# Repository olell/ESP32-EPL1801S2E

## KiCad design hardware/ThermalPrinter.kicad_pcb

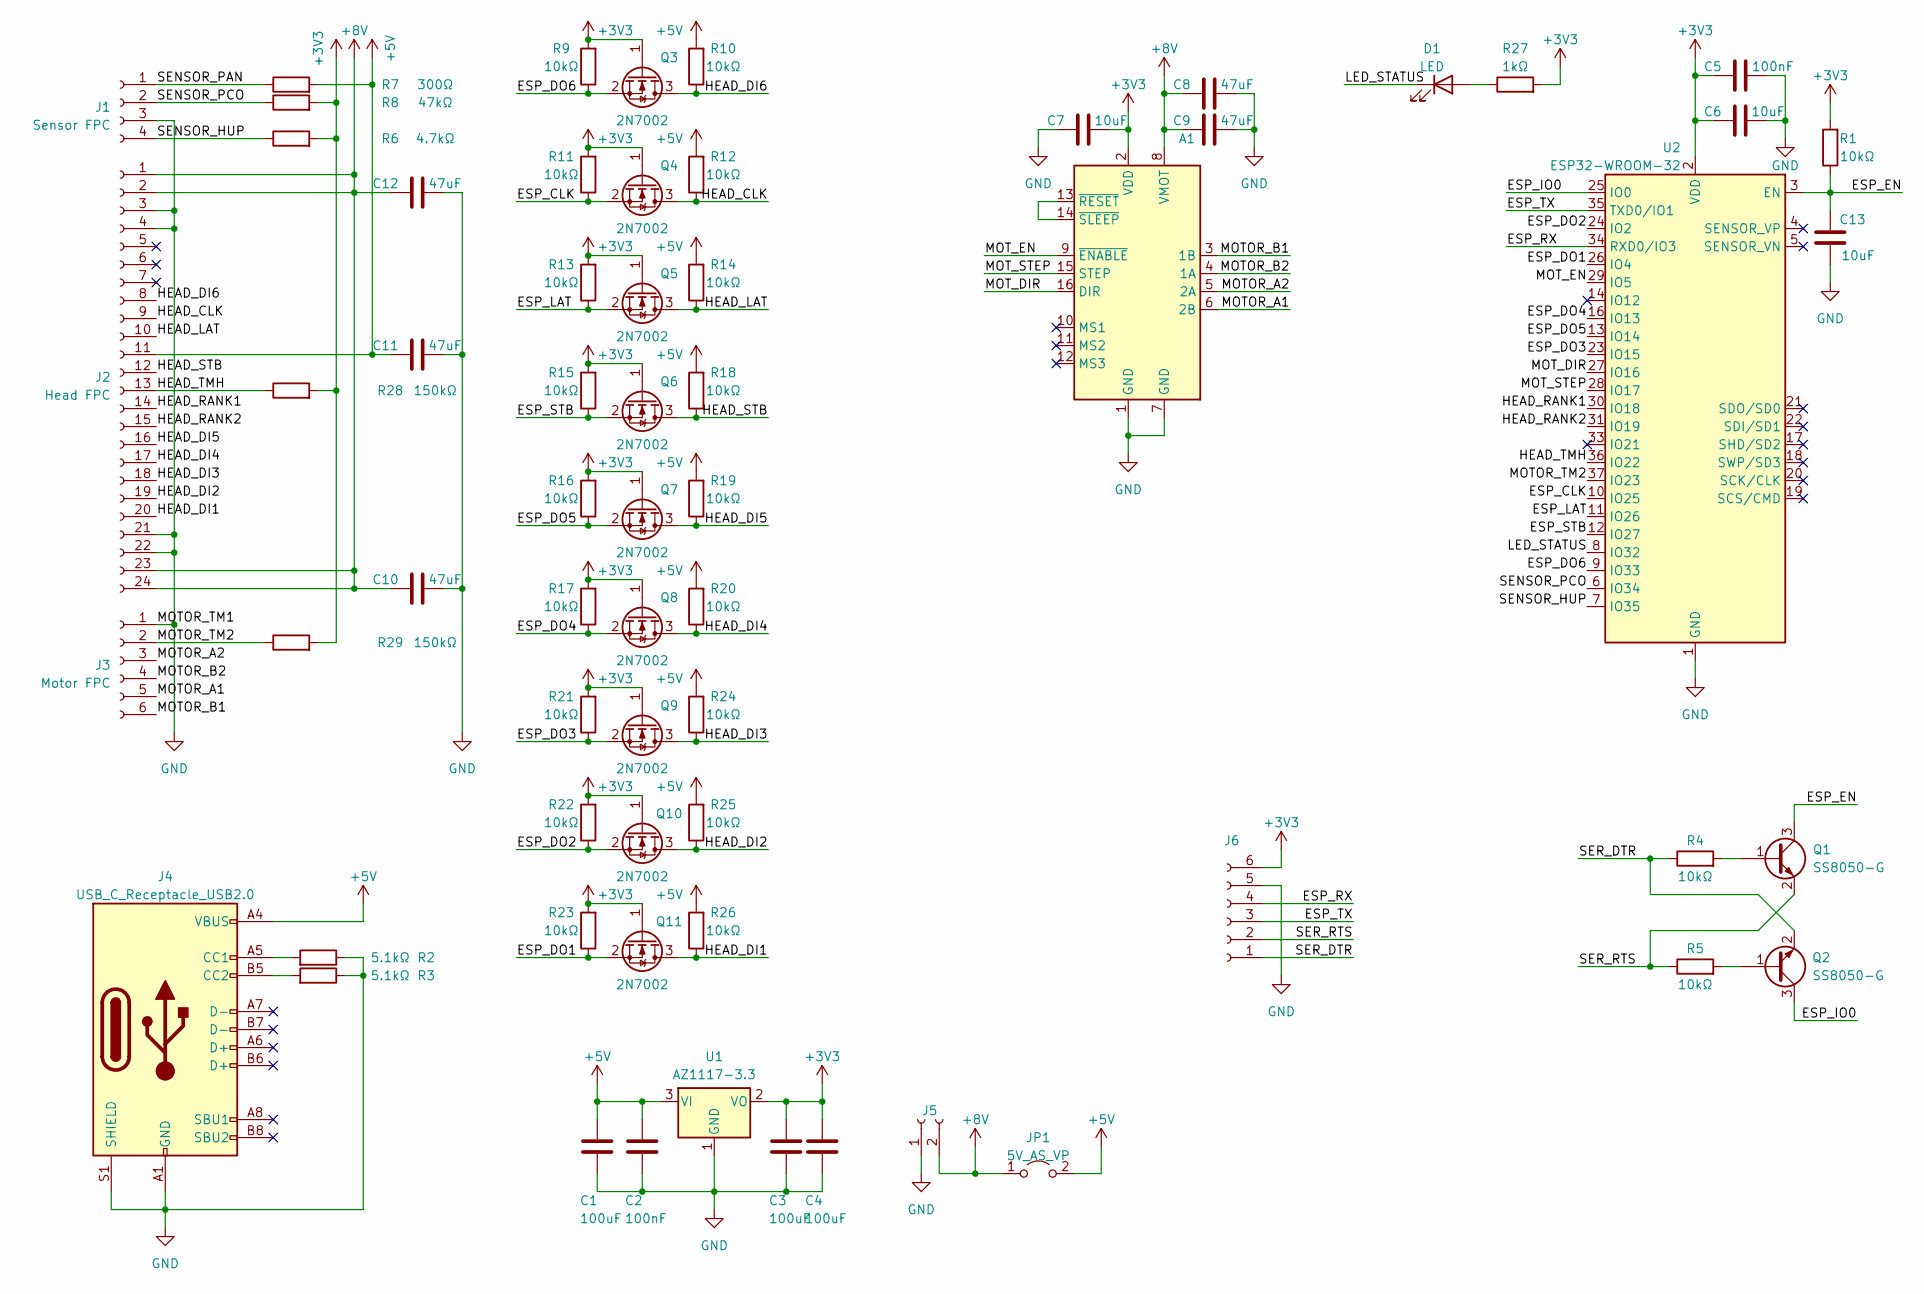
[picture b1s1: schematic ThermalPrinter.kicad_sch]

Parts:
A1: Pololu_Breakout_A4988; Pololu_Breakout-16_15.2x20.3mm
C1, C3, C4: 100uF; C_1206_3216Metric; LCSC C15008
C2, C5: 100nF; C_0603_1608Metric; LCSC C14663
C6, C7, C13: 10uF; C_0603_1608Metric; LCSC C19702
C8, C9, C10, C11, C12: 47uF; C_1206_3216Metric; LCSC C96123
D1: LED; LED_0603_1608Metric; LCSC C2286
J1: Sensor FPC; Molex_200528-0040_1x04-1MP_P1.00mm_Horizontal; LCSC C13750
J2: Head FPC; Molex_200528-0240_1x24-1MP_P1.00mm_Horizontal; LCSC C262376
J3: Motor FPC; Molex_200528-0060_1x06-1MP_P1.00mm_Horizontal; LCSC C72727
J4: USB_C_Receptacle_USB2.0; USB_C_Receptacle_HRO_TYPE-C-31-M-12; LCSC C2988369
J5: Conn_01x02_Socket; PinHeader_1x02_P2.54mm_Vertical
J6: Conn_01x06_Socket; PinSocket_1x06_P2.54mm_Vertical
JP1: 5V_AS_VP; PinSocket_1x02_P2.54mm_Vertical
Q1, Q2: SS8050-G; SOT-23; LCSC C2150
Q3, Q4, Q5, Q6, Q7, Q8, Q9, Q10, Q11: 2N7002; SOT-23; LCSC C8545
R1, R4, R5, R9, R10, R11, R12, R13, R14, R15, R16, R17, R18, R19, R20, R21, R22, R23, R24, R25, R26: 10kΩ; R_0603_1608Metric; LCSC C25804
R2, R3: 5.1kΩ; R_0603_1608Metric; LCSC C23186
R6: 4.7kΩ; R_0603_1608Metric; LCSC C23162
R7: 300Ω; R_0603_1608Metric; LCSC C23025
R8: 47kΩ; R_0603_1608Metric; LCSC C25819
R27: 1kΩ; R_0603_1608Metric; LCSC C21190
R28, R29: 150kΩ; R_0603_1608Metric; LCSC C22807
U1: AZ1117-3.3; SOT-223-3_TabPin2; LCSC C6186
U2: ESP32-WROOM-32; LCSC C529582

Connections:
+3V3: A1.2 (VDD), C3.1, C4.1, C5.1, C6.1, C7.2, J6.6, Q3.1 (G), Q4.1 (G), Q5.1 (G), Q6.1 (G), Q7.1 (G), Q8.1 (G), Q9.1 (G), Q10.1 (G), Q11.1 (G), R1.2, R6.2, R8.2, R9.2, R11.2, R13.2, R15.2, R16.2, R17.2, R21.2, R22.2, R23.2, R27.2, R28.2, R29.2, U1.2 (VO), U2.2 (VDD)
+5V: C1.1, C2.1, C11.1, J2.11, J4.A4 (VBUS), J4.A9 (VBUS), J4.B4 (VBUS), J4.B9 (VBUS), JP1.2 (B), R7.2, R10.2, R12.2, R14.2, R18.2, R19.2, R20.2, R24.2, R25.2, R26.2, U1.3 (VI)
+8V: A1.8 (VMOT), C8.1, C9.1, C10.1, C12.1, J2.1, J2.2, J2.23, J2.24, J5.2, JP1.1 (A)
/ESP_CLK: Q4.2 (S), R11.1, U2.10 (IO25)
/ESP_DO1: Q11.2 (S), R23.1, U2.26 (IO4)
/ESP_DO2: Q10.2 (S), R22.1, U2.24 (IO2)
/ESP_DO3: Q9.2 (S), R21.1, U2.23 (IO15)
/ESP_DO4: Q8.2 (S), R17.1, U2.16 (IO13)
/ESP_DO5: Q7.2 (S), R16.1, U2.13 (IO14)
/ESP_DO6: Q3.2 (S), R9.1, U2.9 (IO33)
/ESP_EN: C13.2, Q1.3 (C), R1.1, U2.3 (EN)
/ESP_IO0: Q2.3 (C), U2.25 (IO0)
/ESP_LAT: Q5.2 (S), R13.1, U2.11 (IO26)
/ESP_RX: J6.4, U2.34 (RXD0/IO3)
/ESP_STB: Q6.2 (S), R15.1, U2.12 (IO27)
/ESP_TX: J6.3, U2.35 (TXD0/IO1)
/HEAD_CLK: J2.9, Q4.3 (D), R12.1
/HEAD_DI1: J2.20, Q11.3 (D), R26.1
/HEAD_DI2: J2.19, Q10.3 (D), R25.1
/HEAD_DI3: J2.18, Q9.3 (D), R24.1
/HEAD_DI4: J2.17, Q8.3 (D), R20.1
/HEAD_DI5: J2.16, Q7.3 (D), R19.1
/HEAD_DI6: J2.8, Q3.3 (D), R10.1
/HEAD_LAT: J2.10, Q5.3 (D), R14.1
/HEAD_RANK1: J2.14, U2.30 (IO18)
/HEAD_RANK2: J2.15, U2.31 (IO19)
/HEAD_STB: J2.12, Q6.3 (D), R18.1
/HEAD_TMH: J2.13, R28.1, U2.36 (IO22)
/LED_STATUS: D1.1 (K), U2.8 (IO32)
/MOTOR_A1: A1.6 (2B), J3.5
/MOTOR_A2: A1.5 (2A), J3.3
/MOTOR_B1: A1.3 (1B), J3.6
/MOTOR_B2: A1.4 (1A), J3.4
/MOTOR_TM2: J3.2, R29.1, U2.37 (IO23)
/MOT_DIR: A1.16 (DIR), U2.27 (IO16)
/MOT_EN: A1.9 (~ENABLE), U2.29 (IO5)
/MOT_STEP: A1.15 (STEP), U2.28 (IO17)
/SENSOR_HUP: J1.4, R6.1, U2.7 (IO35)
/SENSOR_PAN: J1.1, R7.1
/SENSOR_PCO: J1.2, R8.1, U2.6 (IO34)
/SER_DTR: J6.1, Q2.2 (E), R4.1
/SER_RTS: J6.2, Q1.2 (E), R5.1
GND: A1.1 (GND), A1.7 (GND), C1.2, C2.2, C3.2, C4.2, C5.2, C6.2, C7.1, C8.2, C9.2, C10.2, C11.2, C12.2, C13.1, J1.3, J2.3, J2.4, J2.21, J2.22, J3.1, J4.A1 (GND), J4.A12 (GND), J4.B1 (GND), J4.B12 (GND), J4.S1 (SHIELD), J5.1, J6.5, R2.1, R3.1, U1.1 (GND), U2.1 (GND), U2.15 (GND), U2.38 (GND), U2.39 (GND)
unnamed: A1.13 (~RESET), A1.14 (~SLEEP)
unnamed: D1.2 (A), R27.1
unnamed: J4.A5 (CC1), R2.2
unnamed: J4.B5 (CC2), R3.2
unnamed: Q1.1 (B), R4.2
unnamed: Q2.1 (B), R5.2

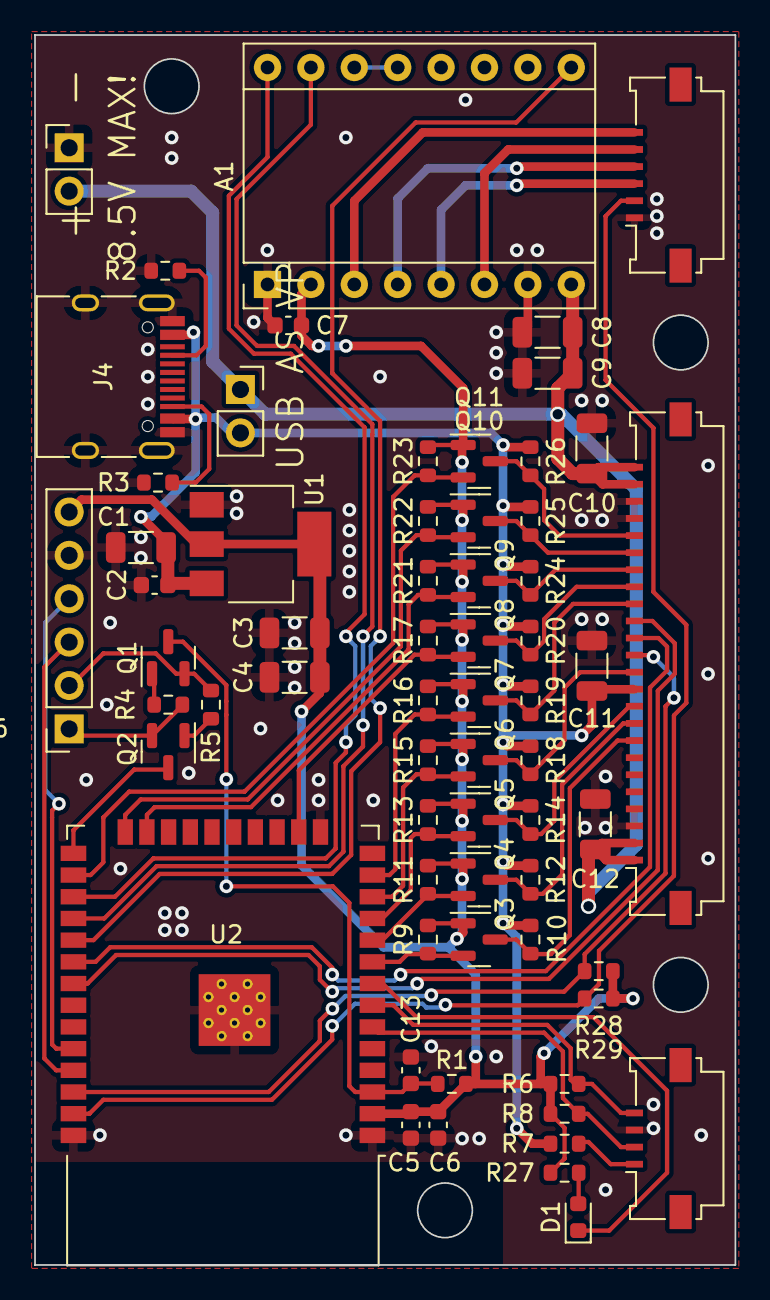
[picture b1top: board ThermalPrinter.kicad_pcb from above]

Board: 2 copper layers, 41.0 x 72.0 mm, 64 parts (0 on the bottom side), 49 nets.

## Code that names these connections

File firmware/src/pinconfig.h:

/**
 * ESP32 Driver for EPL1801S2E
 * Pin configuration
 *
 * (C) 2023 Ole Lange
 */

#define PIN_MOTOR_STEP 17
#define PIN_MOTOR_DIRECTION 16
#define PIN_MOTOR_ENABLE 5

#define PIN_SENSOR_PAPER 34
#define PIN_SENSOR_HEAD 35

#define PIN_THERMISTOR_MOTOR 23
#define PIN_THERMISTOR_HEAD 39

#define PIN_HEAD_DATA1 4
#define PIN_HEAD_DATA2 21
#define PIN_HEAD_DATA3 15
#define PIN_HEAD_DATA4 13
#define PIN_HEAD_DATA5 14
#define PIN_HEAD_DATA6 33
#define PIN_HEAD_CLK 25
#define PIN_HEAD_LAT 26
#define PIN_HEAD_STB 27
#define PIN_HEAD_RANK1 18
#define PIN_HEAD_RANK2 19

#define PIN_LED_STATUS 32

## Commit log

2023-05-01 Added gitignore
2023-05-01 Added initial files
2023-05-01 Add vscode extension file
2023-05-01 Change code to match c++ naming scheme
2023-05-01 Add paper and head sensor read
2023-05-01 Implemented thermistor read
2023-05-01 Completed pin config
2023-05-01 Missed change fixed
2023-05-01 Moved driver code to subdir
2023-05-01 Implemented head functions
2023-05-02 Added dividing + row sum to strobe time calc
2023-05-02 Added jupyter dir to gitignore
2023-05-19 Cleanup
2023-05-20 Dump first working prototype
